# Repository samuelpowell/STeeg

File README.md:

# STeeg

# Startup
  - tPOR = 2^18 x tclk
  - tRST = 2 x tclk

# Form factor

 - To fit Takachi HEN110512 (S/B) external W111.2 x H54.7 x D120mm, internal 99.2W x H49.7 x D116mm.

# Configuration

  - Referential montage using SRB1 internally routed negative inputs.
  - Internal BIAS amplifier is used to reject interference and set patien common mode, components are chosen in bias amplifier feedback path to attain sufficient bandiwdth.
  - RC network on input is a low pass filter with differential capacitor to VREF, assuming fclk = 2.048MHz, the first alias is at fMOD = 1.024MHz and this should have good attenuation.

# Layout, power and passives.

  - AVDD and AVDD1 must be quiet. AVDD1 is the charge pump supply which may have switch transients. AVDD1 and AVSS1 should be starred, and each supply should be bypassed with 10u and 0.1u solid ceramic capacitors.
  - VCAP1 can be MLCC but for improved performance under vibration a tantalum or class 1 (C0G/NPO) should be used.
  - At output, provide VREF and VBIAS for differential capacitance and bias bpins
  - Decoupling capacitors and VCAP1 - VCAP4 should be as close as possible.
  - Optionally split analogue and digital planes, route over the appropriate plane
  - Use COG for differentials
  - 

# Architecture
 - 6-XV quiet input, isolated
 - 
# Component choices

 - Analogue LDO (TPS717 selected)
  - EVM uses TPS73225 on bipolar, 30uV (10-100kHz), 1% accuracy, 37dB @ 10kHz, 58dB @ 100Hz
  - TPS793 200mA, 70dB @ 10kHz, 112mv dropout, SOT-23
  - TPS77350, 55dB @ 1kHz, 30uV
  - TPS717XX, 70dB @ 1kHz, 67dB @100kHz, 30uV (100Hz - 100kHz), SOT-23

# Chaining multiple channels

# Notes

  - ADD LEDs
  - ADD Test Points
 - MICROCONTROLLER BOOT
 - MCU PROG
 - optional 3.3v external

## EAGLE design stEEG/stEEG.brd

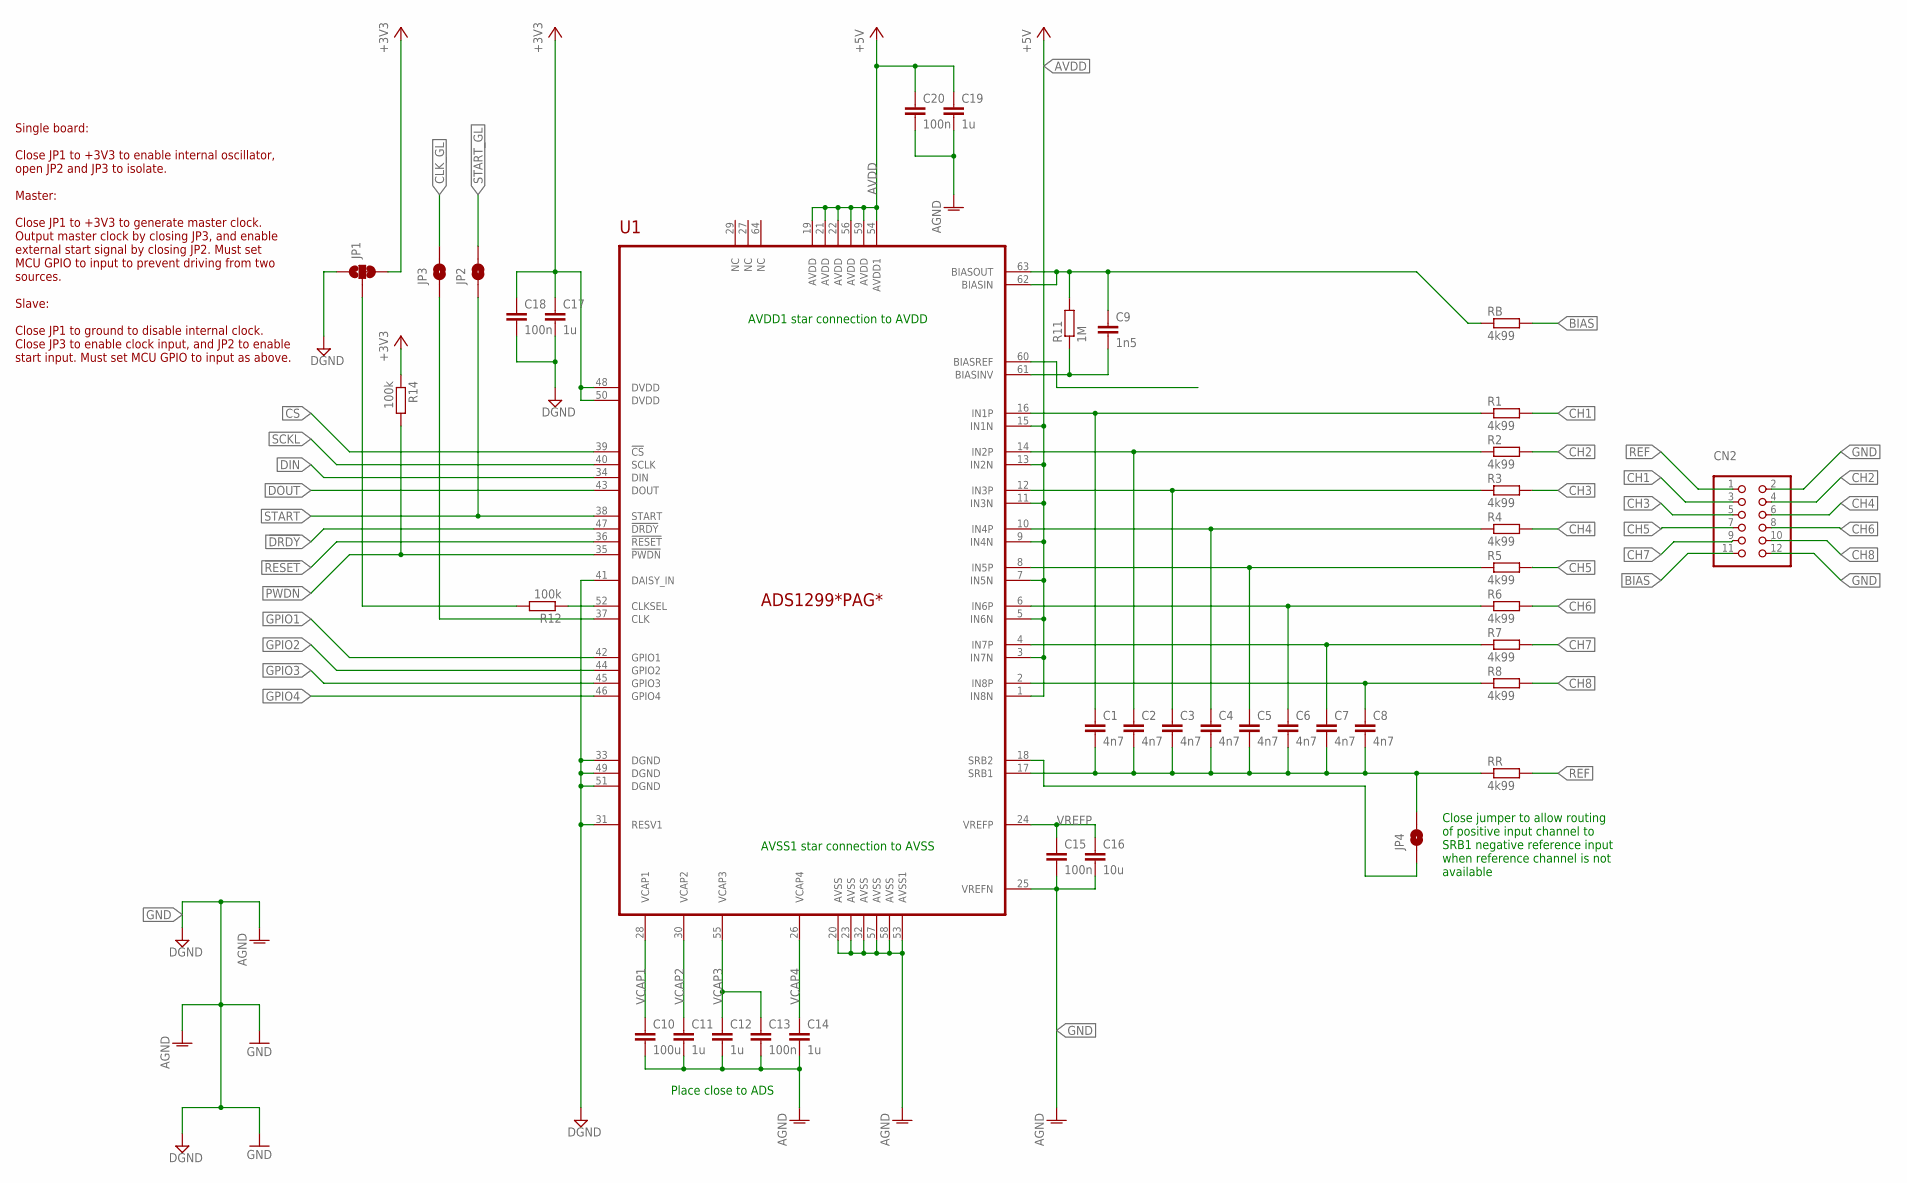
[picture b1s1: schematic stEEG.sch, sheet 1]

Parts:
C1, C2, C3, C4, C5, C6, C7, C8: 4n7; C0402
C9: 1n5; C0402
C10: 100u; C1206
C11, C12, C14, C17, C19: 1u; C0603
C13, C15, C18, C20: 100n; C0402
C16: 10u; C0603
CN2: PINHD-2X6/90; 2X06/90
JP1: JUMPER-SMT_3_1-NC_TRACE_SILK; SMT-JUMPER_3_1-NC_TRACE_SILK
JP2, JP3, JP4: JUMPER-SMT_2_NO_SILK; SMT-JUMPER_2_NO_SILK
R1, R2, R3, R4, R5, R6, R7, R8: 4k99; R0402
R11: 1M; R0402
R12, R14: 100k; R0402
RB: 4k99; R0402
RR: 4k99; R0402
U1: ADS1299*PAG*; PAG-PQFP64

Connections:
!CS: U1.39 (!CS); also elsewhere on the board
!DRDY: U1.47 (!DRDY); also elsewhere on the board
!PWDN: R14.2, U1.35 (!PWDN); also elsewhere on the board
!RESET: U1.36 (!RESET); also elsewhere on the board
+3V3: C17.1, C18.1, JP1.3, R14.1, U1.48 (DVDD), U1.50 (DVDD); also elsewhere on the board
AVDD: C19.1, C20.1, U1.1 (IN8N), U1.3 (IN7N), U1.5 (IN6N), U1.7 (IN5N), U1.9 (IN4N), U1.11 (IN3N), U1.13 (IN2N), U1.15 (IN1N), U1.19 (AVDD), U1.21 (AVDD), U1.22 (AVDD), U1.54 (AVDD1), U1.56 (AVDD), U1.59 (AVDD); also elsewhere on the board
BIAS: CN2.11, RB.2
CH1: CN2.3, R1.2
CH2: CN2.4, R2.2
CH3: CN2.5, R3.2
CH4: CN2.6, R4.2
CH5: CN2.7, R5.2
CH6: CN2.8, R6.2
CH7: CN2.9, R7.2
CH8: CN2.10, R8.2
CLK_GL: JP3.2; also elsewhere on the board
DIN: U1.34 (DIN); also elsewhere on the board
DOUT: U1.43 (DOUT); also elsewhere on the board
GND: C10.2, C11.2, C12.2, C13.2, C14.2, C15.2, C16.2, C17.2, C18.2, C19.2, C20.2, CN2.2, CN2.12, JP1.1, U1.20 (AVSS), U1.23 (AVSS), U1.25 (VREFN), U1.31 (RESV1), U1.32 (AVSS), U1.33 (DGND), U1.41 (DAISY_IN), U1.49 (DGND), U1.51 (DGND), U1.53 (AVSS1), U1.57 (AVSS), U1.58 (AVSS); also elsewhere on the board
GPIO1: U1.42 (GPIO1)
GPIO2: U1.44 (GPIO2)
GPIO3: U1.45 (GPIO3)
GPIO4: U1.46 (GPIO4)
unnamed: C1.1, R1.1, U1.16 (IN1P)
unnamed: R12.1, U1.52 (CLKSEL)
unnamed: C3.1, R3.1, U1.12 (IN3P)
unnamed: C4.1, R4.1, U1.10 (IN4P)
unnamed: C9.2, R11.1, U1.61 (BIASINV)
unnamed: C6.1, R6.1, U1.6 (IN6P)
unnamed: C7.1, R7.1, U1.4 (IN7P)
unnamed: C9.1, R11.2, RB.1, U1.62 (BIASIN), U1.63 (BIASOUT)
unnamed: C2.1, R2.1, U1.14 (IN2P)
unnamed: C5.1, R5.1, U1.8 (IN5P)
unnamed: C8.1, R8.1, U1.2 (IN8P)
unnamed: JP4.1, U1.18 (SRB2)
unnamed: JP1.2, R12.2
unnamed: JP3.1, U1.37 (CLK)
REF: CN2.1, RR.2
SCKL: U1.40 (SCLK); also elsewhere on the board
START: JP2.1, U1.38 (START); also elsewhere on the board
START_GL: JP2.2; also elsewhere on the board
VCAP1: C10.1, U1.28 (VCAP1)
VCAP2: C11.1, U1.30 (VCAP2)
VCAP3: C12.1, C13.1, U1.55 (VCAP3)
VCAP4: C14.1, U1.26 (VCAP4)
VREFP: C15.1, C16.1, U1.24 (VREFP)
VREFX: C1.2, C2.2, C3.2, C4.2, C5.2, C6.2, C7.2, C8.2, JP4.2, RR.1, U1.17 (SRB1)

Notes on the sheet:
AVDD1 star connection to AVDD
AVSS1 star connection to AVSS
Place close to ADS
Close jumper to allow routing of positive input channel to SRB1 negative reference input when reference channel is not available
Single board: Close JP1 to +3V3 to enable internal oscillator, open JP2 and JP3 to isolate. Master: Close JP1 to +3V3 to generate master clock. Output master clock by closing JP3, and enable external start signal by closing JP2. Must set MCU GPIO to input to prevent driving from two sources. Slave: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

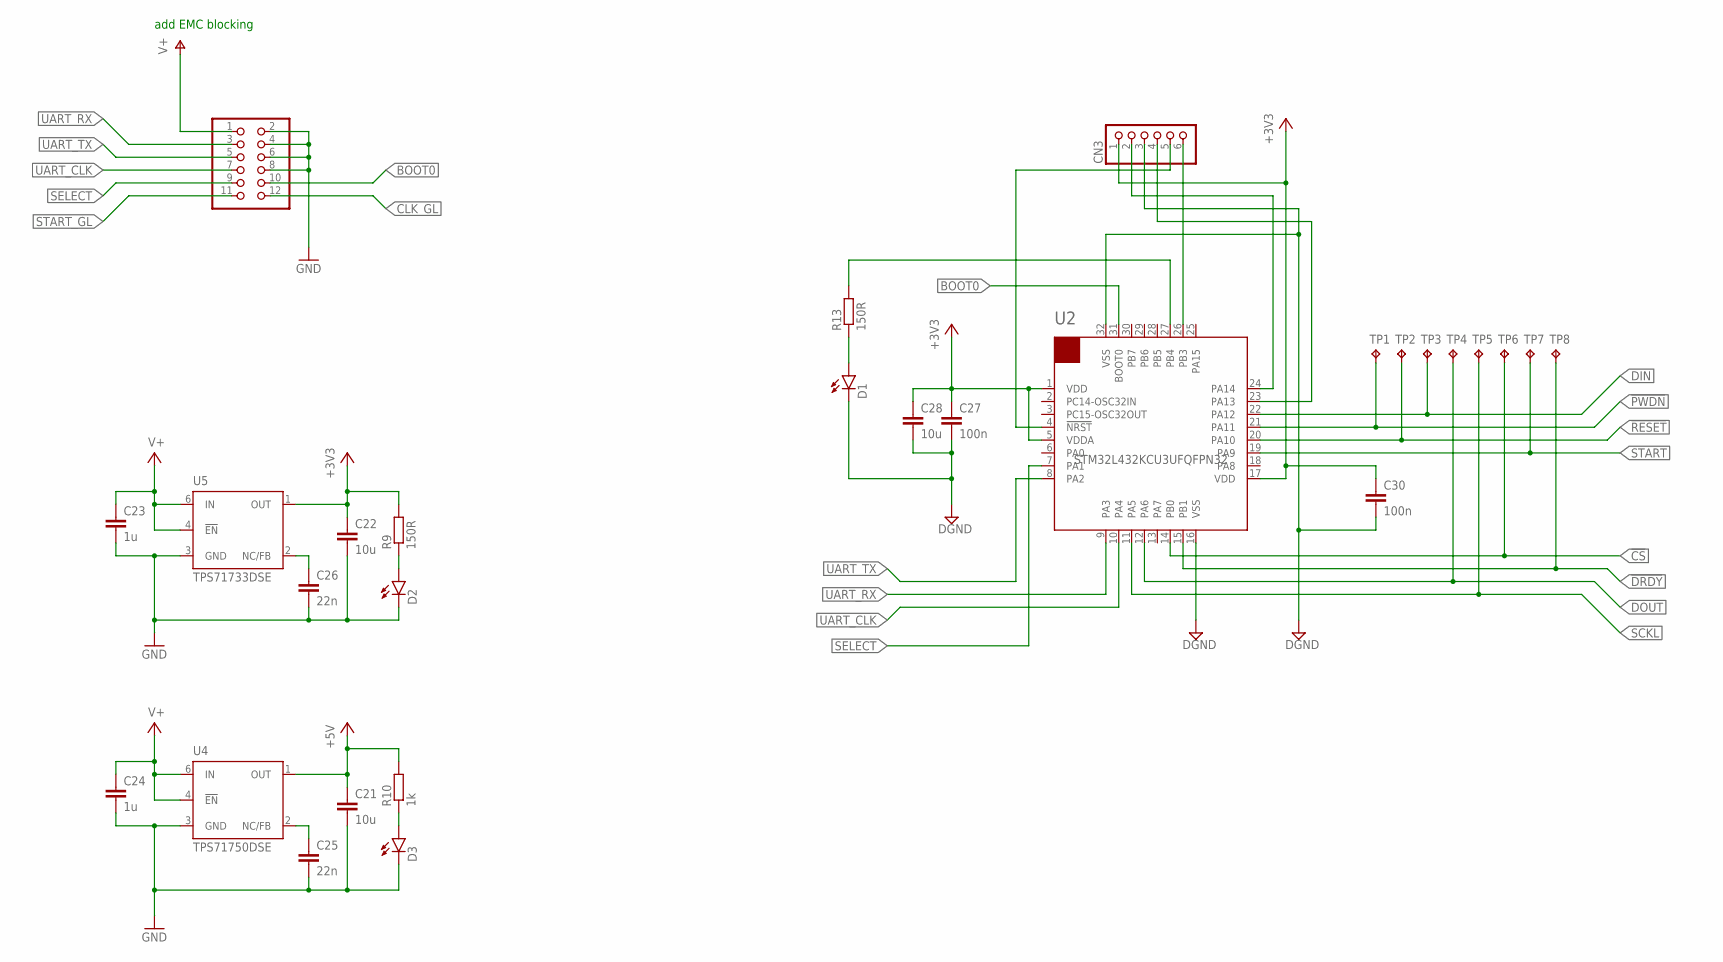
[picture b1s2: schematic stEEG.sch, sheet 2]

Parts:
C21, C22: 10u; C0805
C23, C24: 1u; C0603
C25, C26: 22n; C0402
C27, C30: 100n; C0402
C28: 10u; C0603
CN1: PINHD-2X6/90; 2X06/90
CN3: PINHD-1X6; 1X06
D1, D2, D3: LED0603; CHIP-LED0603
R9, R13: 150R; R0402
R10: 1k; R0402
TP1, TP2, TP3, TP4, TP5, TP6, TP7, TP8: TPTP10R; TP10R
U2: STM32L432KCU3UFQFPN32; QFN50P500X500X60-32
U4: TPS71750DSE; WSON-DSE
U5: TPS71733DSE; WSON-DSE

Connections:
!CS: TP6.TP, U2.14 (PB0); also elsewhere on the board
!DRDY: TP8.TP, U2.15 (PB1); also elsewhere on the board
!PWDN: TP1.TP, U2.21 (PA11); also elsewhere on the board
!RESET: TP2.TP, U2.20 (PA10); also elsewhere on the board
+3V3: C22.1, C27.1, C28.1, C30.1, CN3.1, R9.2, U2.1 (VDD), U2.5 (VDDA), U2.17 (VDD), U5.1 (OUT); also elsewhere on the board
AVDD: C21.1, R10.2, U4.1 (OUT); also elsewhere on the board
BOOT0: CN1.10, U2.31 (BOOT0)
CLK_GL: CN1.12; also elsewhere on the board
DIN: TP3.TP, U2.22 (PA12); also elsewhere on the board
DOUT: TP4.TP, U2.12 (PA6); also elsewhere on the board
GND: C21.2, C22.2, C23.2, C24.2, C25.2, C26.2, C27.2, C28.2, C30.2, CN1.2, CN1.4, CN1.6, CN1.8, CN3.3, D1.C, D2.C, D3.C, U2.16 (VSS), U2.32 (VSS), U4.3 (GND), U5.3 (GND); also elsewhere on the board
unnamed: D1.A, R13.1
unnamed: CN3.4, U2.23 (PA13)
unnamed: C26.1, U5.2 (NC/FB)
unnamed: CN3.2, U2.24 (PA14)
unnamed: CN3.6, U2.26 (PB3)
unnamed: CN3.5, U2.4 (!NRST)
unnamed: D2.A, R9.1
unnamed: R13.2, U2.27 (PB4)
unnamed: D3.A, R10.1
unnamed: C25.1, U4.2 (NC/FB)
SCKL: TP5.TP, U2.11 (PA5); also elsewhere on the board
SELECT: CN1.9, U2.7 (PA1)
START: TP7.TP, U2.19 (PA9); also elsewhere on the board
START_GL: CN1.11; also elsewhere on the board
UART_CLK: CN1.7, U2.10 (PA4)
UART_RX: CN1.3, U2.9 (PA3)
UART_TX: CN1.5, U2.8 (PA2)
V+: C23.1, C24.1, CN1.1, U4.4 (!EN), U4.6 (IN), U5.4 (!EN), U5.6 (IN)

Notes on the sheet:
add EMC blocking

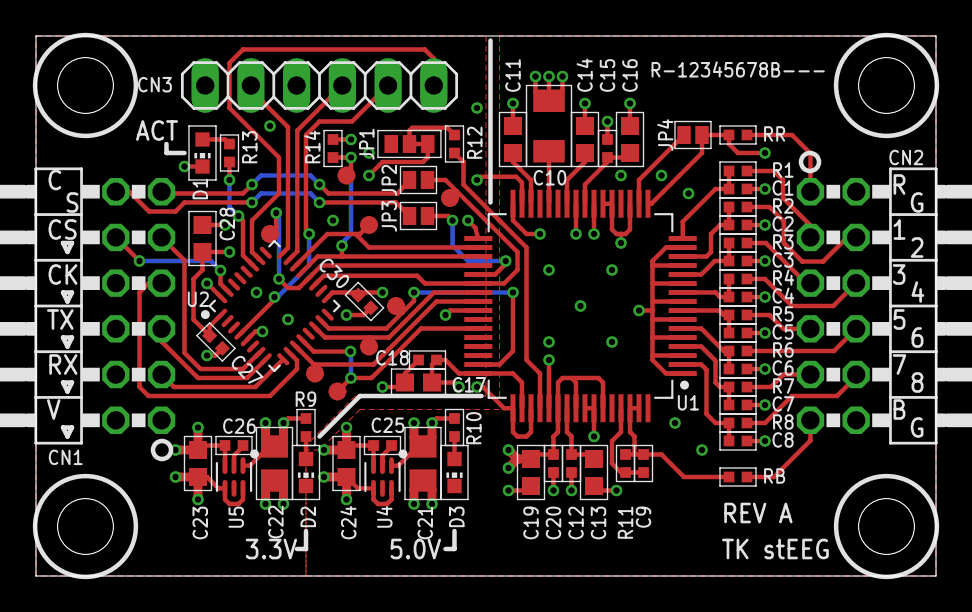
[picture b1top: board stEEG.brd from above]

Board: 4 copper layers, 50.0 x 30.0 mm, 67 parts (0 on the bottom side), 59 nets.

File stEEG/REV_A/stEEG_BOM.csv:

Parts,,Qty,Value,Tolerance,Manufacturer,Part No,Digikiey,Package,Description
"D1, D2, D3",,3,,,OSRAM Opto Semiconductors Inc., LB Q39G-L2OO-35-1, 475-2816-6-ND,0603,LED
CN3,,1,,,Molex,901200126,WM8076-ND,,Pin header straight
"CN1, CN2",,2,,,Molex,10-88-3121,WM23740-ND,,Pin header 90 deg
"R12, R14",,2,100k,"1%, 0.0625W, 50V, 400ppm",Generic,,,0402,Resistor
"C13, C15, C18, C20, C27, C30",,6,100n,"10%, X7R, 16V",Generic,,,0402,Capacitor
C10,,1,100u,"10%, X5R, 6.3V",Murata,GRM31CR60J107KE39L,490-13982-1-ND,1206,Capacitor
"C16, C28",,2,10u,"10%, X5R, 16V",Murata,GRM188R61C106KAALD,490-10728-1-ND,0603,Capacitor
"C21, C22",,2,10u,"10%, X7S, 16V",Murata,GRM21BC71C106KE11L,490-12756-1-ND,0805,Capacitor
"R9, R13",,2,150R,"1%, 0.0625W, 50V, 400ppm",Generic,,,0402,Resistor
R11,,1,1M,"1%, 0.0625W, 50V, 400ppm",Generic,,,0402,Resistor
R10,,1,1k,"1%, 0.0625W, 50V, 400ppm",Generic,,,0402,Resistor
C9,,1,1n5,"10%, X7R, 50V",Generic,,,0402,Capacitor
"C11, C12, C14, C17, C19, C23, C24",,7,1u,"10%, X7R, 16V",Generic,,,0603,Capacitor
"C25, C26",,2,22n,"10%, X7R, 50V",Generic,,,0402,Capacitor
"R1, R2, R3, R4, R5, R6, R7, R8, RB, RR",,10,4k99,"1%, 0.0625W, 50V, 400ppm",Generic,,,0402,Resistor
"C1, C2, C3, C4, C5, C6, C7, C8",,8,4n7,"10%, X7R, 50V",Generic,,,0402,Capacitor
U1,,1,,,Texas Instruments,ADS1299IPAG,296-35009-ND,TQFP64,"8-Channel, 24-Bit Analog-To-Digital Converter With Integrated EEG Front End"
U2,,1,,,ST Microelectronics,STM32L432KCU3,497-18596-ND,QFN32,Low-power ARM M4 microcontroller
U5,,1,,,Texas Instruments,TPS71733DSE,296-32543-1-ND,SON8,"Low-Noise, High-Bandwidth PSRR, Low-Dropout, 150-mA Linear Regulator"
U4,,1,,,Texas Instruments,TPS71750DSE,296-25447-1-ND,SON8,"Low-Noise, High-Bandwidth PSRR, Low-Dropout, 150-mA Linear Regulator"

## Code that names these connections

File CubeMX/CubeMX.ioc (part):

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Mcu.Name=STM32L432K(B-C)Ux
Mcu.Package=UFQFPN32
Mcu.UserName=STM32L432KCUx
PA1.GPIOParameters=GPIO_Label
PA1.GPIO_Label=SELECT
PA1.Signal=GPIO_Input
PA10.GPIOParameters=GPIO_Label
PA10.GPIO_Label=NRST
PA10.Signal=GPIO_Output
PA11.GPIOParameters=GPIO_Label
PA11.GPIO_Label=NPWDN
PA11.Signal=GPIO_Output
PA12.Mode=Full_Duplex_Master
PA12.Signal=SPI1_MOSI
PA13\ (JTMS-SWDIO).Mode=Trace_Asynchronous_SW
PA13\ (JTMS-SWDIO).Signal=SYS_JTMS-SWDIO
PA14\ (JTCK-SWCLK).Mode=Trace_Asynchronous_SW
PA14\ (JTCK-SWCLK).Signal=SYS_JTCK-SWCLK
PA2.Mode=Synchronous
PA2.Signal=USART2_TX
PA3.Mode=Synchronous
PA3.Signal=USART2_RX
PA4.Mode=Synchronous
PA4.Signal=USART2_CK
PA5.Mode=Full_Duplex_Master
PA5.Signal=SPI1_SCK
PA6.Mode=Full_Duplex_Master
PA6.Signal=SPI1_MISO
PA9.GPIOParameters=GPIO_Label
PA9.GPIO_Label=START
PA9.Signal=GPIO_Output
PB0.Mode=NSS_Signal_Hard_Output
PB0.Signal=SPI1_NSS
PB1.GPIOParameters=GPIO_Label
PB1.GPIO_Label=NDRDY
PB1.Signal=GPIO_Input
PB3\ (JTDO-TRACESWO).Mode=Trace_Asynchronous_SW
PB3\ (JTDO-TRACESWO).Signal=SYS_JTDO-SWO
PB4\ (NJTRST).GPIOParameters=GPIO_Label
PB4\ (NJTRST).GPIO_Label=LED_ACT
PB4\ (NJTRST).Signal=GPIO_Output
PB6.Mode=Half_duplex(single_wire_mode)
PB6.Signal=USART1_TX
PB7.Mode=Mode_PVD_Ext
PB7.Signal=SYS_PVD_IN
PH3-BOOT0.GPIOParameters=GPIO_Label
PH3-BOOT0.GPIO_Label=BOOT0
PH3-BOOT0.Signal=GPIO_Input
RCC.HSE_VALUE=8000000
RCC.SYSCLKFreq_VALUE=80000000
RCC.SYSCLKSource=RCC_SYSCLKSOURCE_PLLCLK
board=custom

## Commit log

2019-05-06 Initial design, pass ERC, DRC
2019-05-06 Tweak silk, add CAM, generate REV_A mfg
2019-05-06 Save ater RevA
2019-05-06 Add images
2019-05-06 Create manufacture
